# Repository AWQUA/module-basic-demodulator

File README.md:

# module-basic-demodulator

### This repo contains the schematic and board layout for a simple demodulator. What do we mean by that? As Wikipedia notes, a demodulator is "an electronic circuit...that is used to recover the information content from [a] modulated carrier wave." Consider a typical TV remote -- it encodes signals in pulses of infrared light to communicate with with the TV. But the environment the remote is in might have other sources of infrared light, so how is the TV able to "listen to" the remote while ignoring ambient IR light signals?

### The simple answer is that the TV remote encodes its signals (which are perhaps in the range of 1KHz) with a carrier wave (typically in the range of 34KHz to 56KHz). In turn, the TV filters the signal that its photodiode receives, removing from the signal both frequencies below and above the range of the remote signals (again, ~1KHz for this example).

### We at AWQUA don't worry too much about remote controls, but we are very interested in precision optical sensing application in environments with shifting ambient light conditions -- like monitoring turbidity in surface water. So we put together this basic demodulator board, which combines a passive band-pass filter (passive high-pass and low-pass filters in series) with a full-wave rectifier and smoothing capacitor.

### The board is designed to be flexible -- allowing surface-mount or through-hole components -- while saving you much of the hassle of breadboarding this circuit. Please note that there are no prescribed values for the passive components. Calculators for the filters can be found at http://sim.okawa-denshi.jp/en/CRlowkeisan.htm and http://sim.okawa-denshi.jp/en/CRhikeisan.htm. The smoothing capacitor can have any value; a larger capacitor will have greater smoothing capability but slower discharge curve.

### To help you test things out in software rather before testing with hardware, we've also included a SPICE model of the circuit (designed in LTSPICE IV).

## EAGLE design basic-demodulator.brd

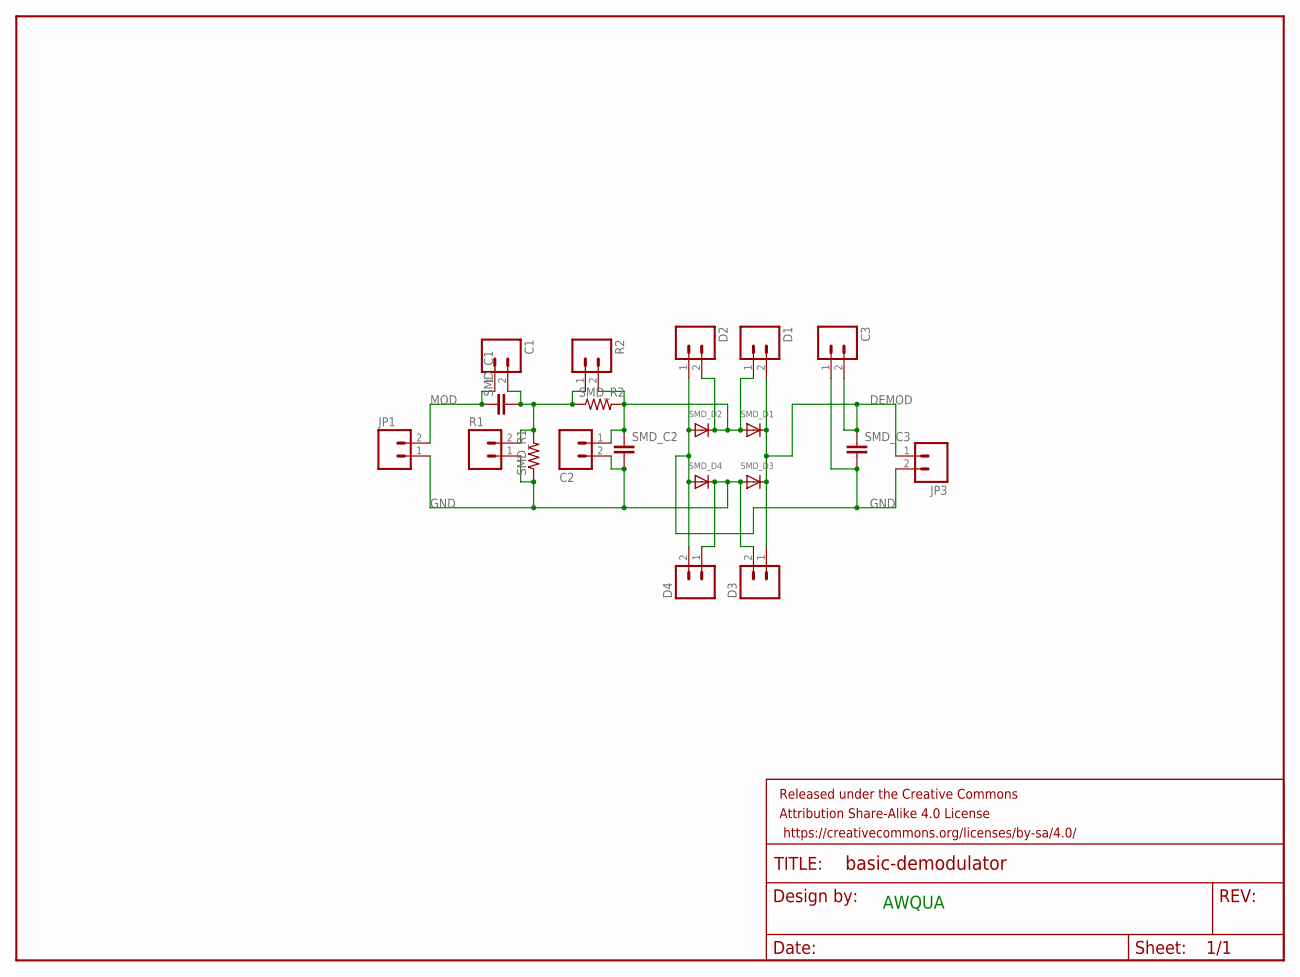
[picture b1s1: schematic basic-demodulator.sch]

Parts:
C1, C2, C3: M02PTH; 1X02
D1, D2, D3, D4: M02PTH; 1X02
FRAME1: FRAME-LETTER; CREATIVE_COMMONS
JP1, JP3: M02PTH; 1X02
R1, R2: M02PTH; 1X02
SMD_C1, SMD_C2, SMD_C3: CAP0603-CAP; 0603-CAP
SMD_D1, SMD_D2, SMD_D3, SMD_D4: DIODESOD-123; SOD-123
SMD_R1, SMD_R2: RESISTOR0603-RES; 0603-RES

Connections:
DEMOD: C3.2, D1.2, D3.1, JP3.1, SMD_C3.1, SMD_D1.C, SMD_D3.C
GND: C2.2, C3.1, D2.1, D3.2, D4.1, D4.2, JP1.1, JP3.2, R1.1, SMD_C2.2, SMD_C3.2, SMD_D2.A, SMD_D3.A, SMD_D4.A, SMD_D4.C, SMD_R1.1
MOD: C1.1, JP1.2, SMD_C1.1
unnamed: C1.2, R1.2, R2.1, SMD_C1.2, SMD_R1.2, SMD_R2.1
PRE_FWR: C2.1, D1.1, D2.2, R2.2, SMD_C2.1, SMD_D1.A, SMD_D2.C, SMD_R2.2

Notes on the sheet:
AWQUA

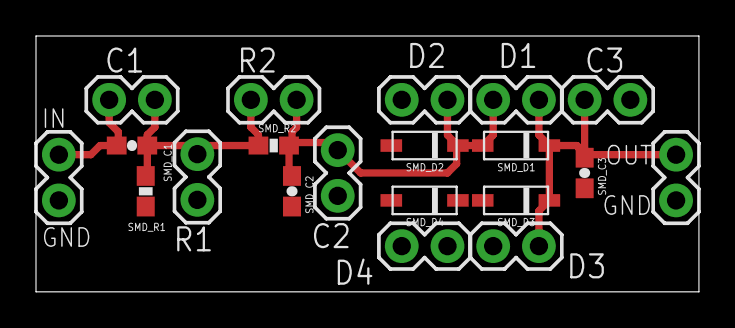
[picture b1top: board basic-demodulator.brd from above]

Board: 2 copper layers, 36.8 x 14.2 mm, 21 parts (0 on the bottom side), 5 nets.

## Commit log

2017-09-21 updated readme, added spice model

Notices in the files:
parts and their libraries:
SparkFun-Passives: Licensing: Creative Commons ShareAlike 4.0 International - https://creativecommons.org/licenses/by-sa/4.0
SparkFun-Aesthetics: Released under the Creative Commons
Attribution Share-Alike 4.0 License
SparkFun-Aesthetics: (https://creativecommons.org/licenses/by-sa/4.0/)
